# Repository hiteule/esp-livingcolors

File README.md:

# ESP LivingColors

An electronic board designed to integrate a LivingColor lamp gen1 in [HomeAssistant].
The board is based on an ESP8266 & [ESPHome] to integrate the LivingColors lamp in HomeAssistant.
The communication with the lamp is managed by an Atmega328 microcontroller & a CC2500 module (2.4ghz RF transceiver).
The ESP8266 & Atmega328 communicate through an I2C bus.

:warning: This board ONLY works with the 1st generation LivingColors.

## PCB

The card must be powered with 5V via the J1 connector.

The Atmega328 can be flashed via JP1. The ESP8266 can be flashed via JP3.
For this, you can use my [ESP/Atmega programmer].

The card was designed with [Eagle].
The additional [libraries] used are:
* 74LVC125AD.lbr
* ATMEGA328P-AU.lbr
* CC2500.lbr
* CONNECTORS.lbr
* ESP-12F.lbr
* TXS0104EPWR.lbr
* regulator.lbr

## Software

### Atmega

The Atmega is controling the LivingColors via RF (like your conventional remote control).
We use Arduino bootloader. If it not already the case, you should install it on your Atmega.
To communicate in RF, we use the library made by [George Knutsel]. Thanks to him!

#### Flash the firmware

* Install the Arduino IDE.
* Put the `LivingColors` library in the right Arduino Library folder.
* Plug the board to your computer with JP1 and the [ESP/Atmega programmer] (for the Atmega, you don't need to power it).
* Open the firmware with the Arduino IDE and flash the Atmega.

Now, you can unplug the Atmega and go to the next step.

### ESP

The ESP is exposing the LivingColors in Home Assisant. To do it, we use [ESPHome].
To do so:
* Install the ESPHome module on HomeAssistant.
* Plug the board to your computer with JP3 and the [ESP/Atmega programmer]. Don't forget to power the programmer with an external power source between 3.3V and 12V.
* In the ESPHome module, create a new device.
* Update your ESPHome device with the `livingcolors.yaml` file.
* Install it on the ESP.

Now you can unplug the ESP from your computer and power the board via JP1.
ESP should boot normally and the LivingColors should be visible in HomeAssistant.

## How to use it ?

### Register the remote address

To be able to communicate with the LivingColors, you need to extract and register the remote address.

* Hold the `SW_LEARN` switch and power on the board to enter in the learning mode.
* The LED will light up for 5 seconds. During this time, place the remote control close to the card and press any button several times.

If the procedure fails, the LED will flash slowly (every 1 second). Repeat the learning procedure.
If the LED is off, the procedure was successful and the remote control address has been extracted and registered. You can now use it :)

### Color cycle mode

To activate the color cycle mode (seen when holding ON remote key), you have to turn on the related light effect on HomeAssistant.

## FAQ

**The LED will flash quickly (every 100ms)**\
The card doesn't know the remote address. You should run a learning procedure. Please see the "How to use it ?" section.

**The LED will flash slowly (every 1s)**\
The remote address learning procedure fail (no address found). You should restart a learning procedure. Place the remote control close to the card and press several buttons.

**Do I need to do a remote address learning procedure every time I launch the card?**\
No, the remote address is saved in the Atmega ROM.

**Can I continue to use the remote control?**\
Yes, you can continue to use the remote control alongside the card.

**Can I register another remote control?**\
Yes, simply launch a remote address learning procedure.
Please note that you can only register one remote control at a time.

[HomeAssistant]: https://www.home-assistant.io
[ESPHome]: https://esphome.io/
[ESP/Atmega programmer]: https://github.com/hiteule/programmer-esp-atmega
[Eagle]: https://www.autodesk.fr/products/eagle
[libraries]: https://github.com/hiteule/eagle-library
[George Knutsel]: http://www.knutsel.org/2010/04/11/using-the-cc2500-arduino-shield

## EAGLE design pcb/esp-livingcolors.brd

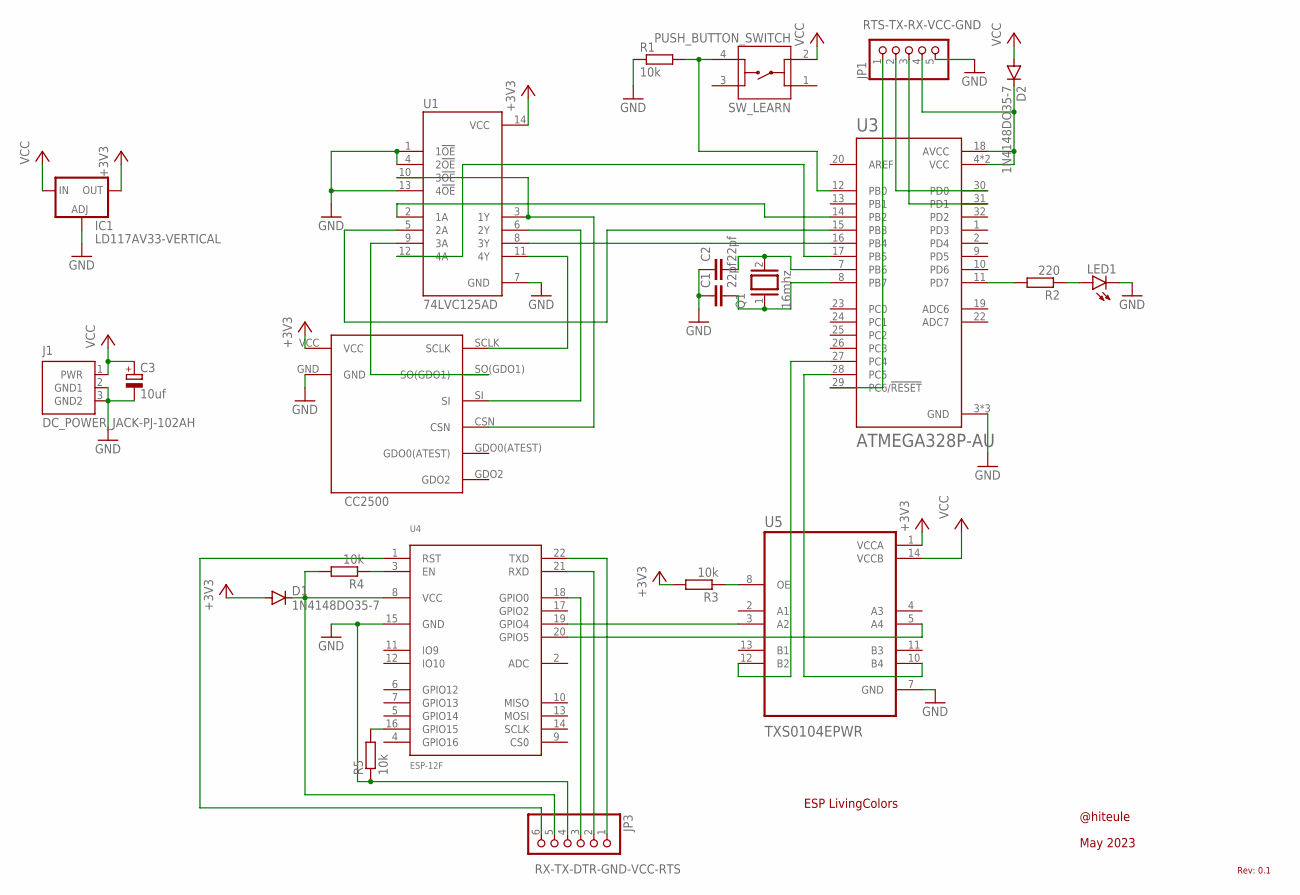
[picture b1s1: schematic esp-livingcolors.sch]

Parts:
C1, C2: 22pf; C025-024X044
C3: 10uf; E2,5-6E
D1, D2: 1N4148DO35-7; DO35-7
IC1: LD117AV33-VERTICAL; TO220S-VERTICAL
J1: DC_POWER_JACK-PJ-102AH; PJ-102AH
JP1: RTS-TX-RX-VCC-GND; 1X05
JP3: RX-TX-DTR-GND-VCC-RTS; 1X06
LED1: LED3MM
Q1: 16mhz; QS
R1, R3, R4: 10k; 0204/7
R2: 220; 0204/7
R5: 10k; 0207/12
SW_LEARN: PUSH_BUTTON_SWITCH
U1: 74LVC125AD; SOIC127P600X175-14N
U3: ATMEGA328P-AU; QFP80P900X900X120-32N
U4: ESP-12F
U5: TXS0104EPWR; SOP65P640X120-14N
U$1: CC2500-ANTENNA-MODULE

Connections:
+3V3: D1.A, IC1.2 (OUT), R3.2, U1.14 (VCC), U5.1 (VCCA), U$1.VCC
GND: C1.1, C2.1, C3.-, IC1.1 (ADJ), J1.2 (GND1), J1.3 (GND2), JP1.5, JP3.4, LED1.K (C), R1.1, R5.1, U1.1 (1!OE!), U1.4 (2!OE!), U1.7 (GND), U1.13 (4!OE!), U3.3 (GND), U3.5 (GND), U3.21 (GND), U4.15 (GND), U5.7 (GND), U$1.GND
unnamed: R1.2, SW_LEARN.4, U3.12 (PB0)
unnamed: C2.2, Q1.2, U3.7 (PB6)
unnamed: C1.2, Q1.1, U3.8 (PB7)
unnamed: R2.2, U3.11 (PD7)
unnamed: LED1.A, R2.1
unnamed: U1.9 (3A), U$1.SO(GDO1)
unnamed: R4.1, U4.3 (EN)
unnamed: U1.3 (1Y), U1.10 (3!OE!), U$1.CSN
unnamed: U1.2 (1A), U3.14 (PB2)
unnamed: U1.5 (2A), U3.15 (PB3)
unnamed: U1.6 (2Y), U$1.SI
unnamed: U1.8 (3Y), U3.16 (PB4)
unnamed: JP3.6, U4.1 (RST)
unnamed: U1.11 (4Y), U$1.SCLK
unnamed: U1.12 (4A), U3.17 (PB5)
unnamed: U3.27 (PC4), U5.12 (B2)
unnamed: R3.1, U5.8 (OE)
unnamed: U3.28 (PC5), U5.10 (B4)
unnamed: U4.19 (GPIO4), U5.3 (A2)
unnamed: U4.20 (GPIO5), U5.5 (A4)
unnamed: JP3.1, U4.22 (TXD)
unnamed: JP3.3, U4.18 (GPIO0)
unnamed: JP3.2, U4.21 (RXD)
unnamed: D1.C, JP3.5, R4.2, U4.8 (VCC)
unnamed: R5.2, U4.16 (GPIO15)
unnamed: D2.C, JP1.4, U3.4 (VCC), U3.6 (VCC), U3.18 (AVCC)
unnamed: JP1.1, U3.29 (PC6/!RESET)
unnamed: JP1.2, U3.30 (PD0)
unnamed: JP1.3, U3.31 (PD1)
VCC: C3.+, D2.A, IC1.3 (IN), J1.1 (PWR), SW_LEARN.2, U5.14 (VCCB)

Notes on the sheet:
ESP LivingColors
@hiteule
May 2023
Rev: 0.1

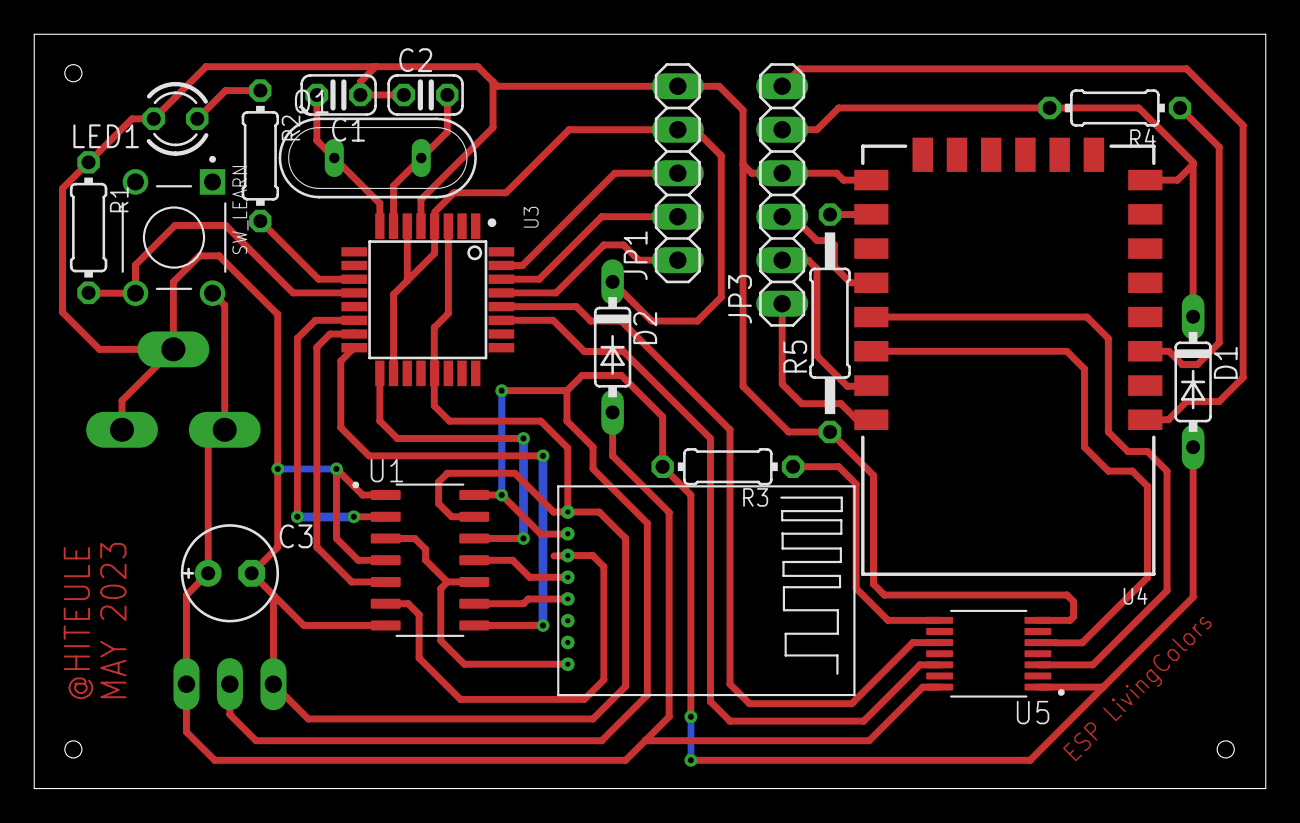
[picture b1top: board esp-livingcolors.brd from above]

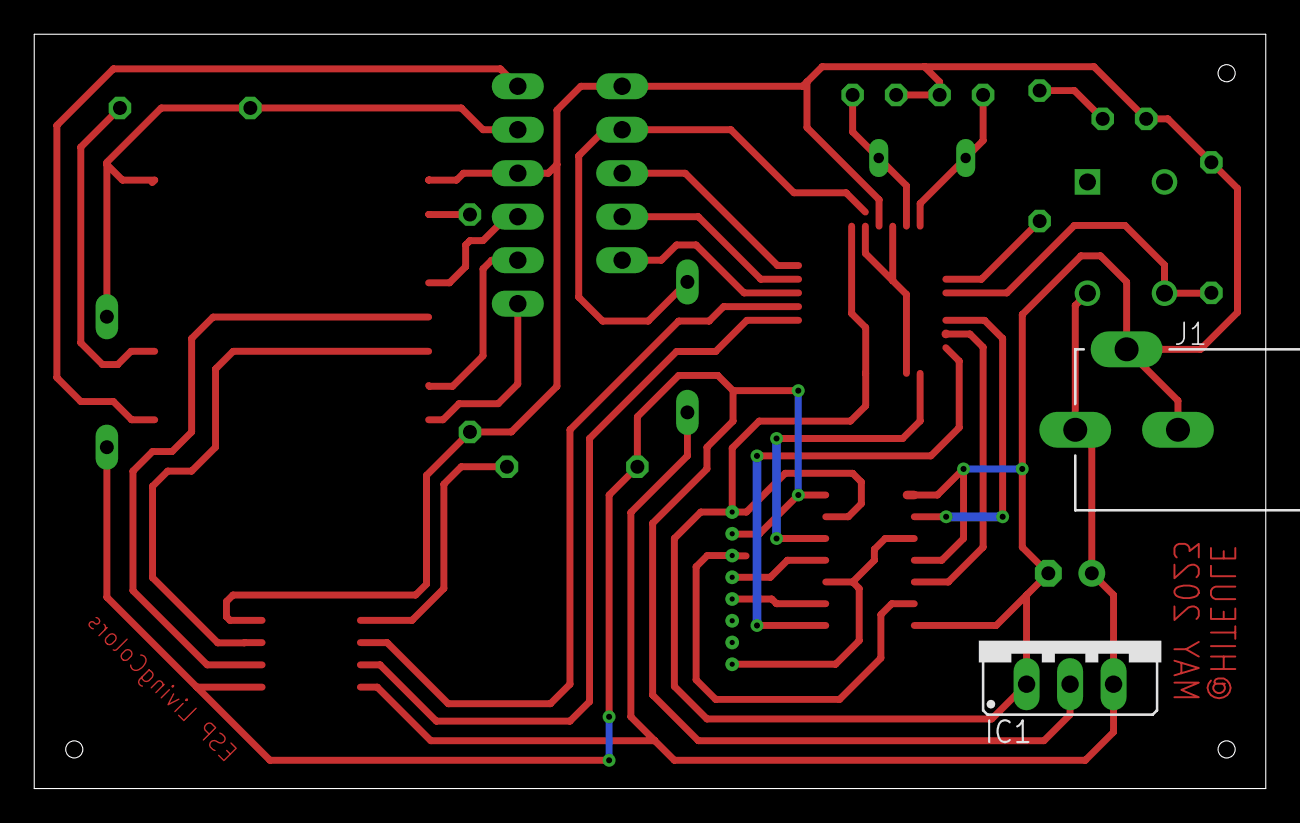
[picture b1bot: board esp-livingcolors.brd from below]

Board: 2 copper layers, 71.9 x 44.1 mm, 22 parts (2 on the bottom side), 32 nets.

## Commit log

2023-05-28 Add software
2023-05-28 Fix readme
2023-07-29 Adding colors rotating mode
2024-06-20 fix(ota): Fix OTA config following 2024.6.0 update
2025-03-29 Move on ESPHome External Components
    Since the removal of the ESPHome Custom Components in the 2025.2.0
    release, this integration no longer works.
    So, let's move on External Components which provide a much cleaner and
    robust integration with ESPHome & HomeAssistant.
    We are taking advantage of this opportunity to expose a native light
    effect for the color cycle mode.
2025-11-20 Handle new LightEffect signature of ESPHome 2025.11
    ESPHome 2025.11 introduced a breaking change to the LightEffect API.
2026-03-19 feat(esphome): Support ESPHome 2026.3
